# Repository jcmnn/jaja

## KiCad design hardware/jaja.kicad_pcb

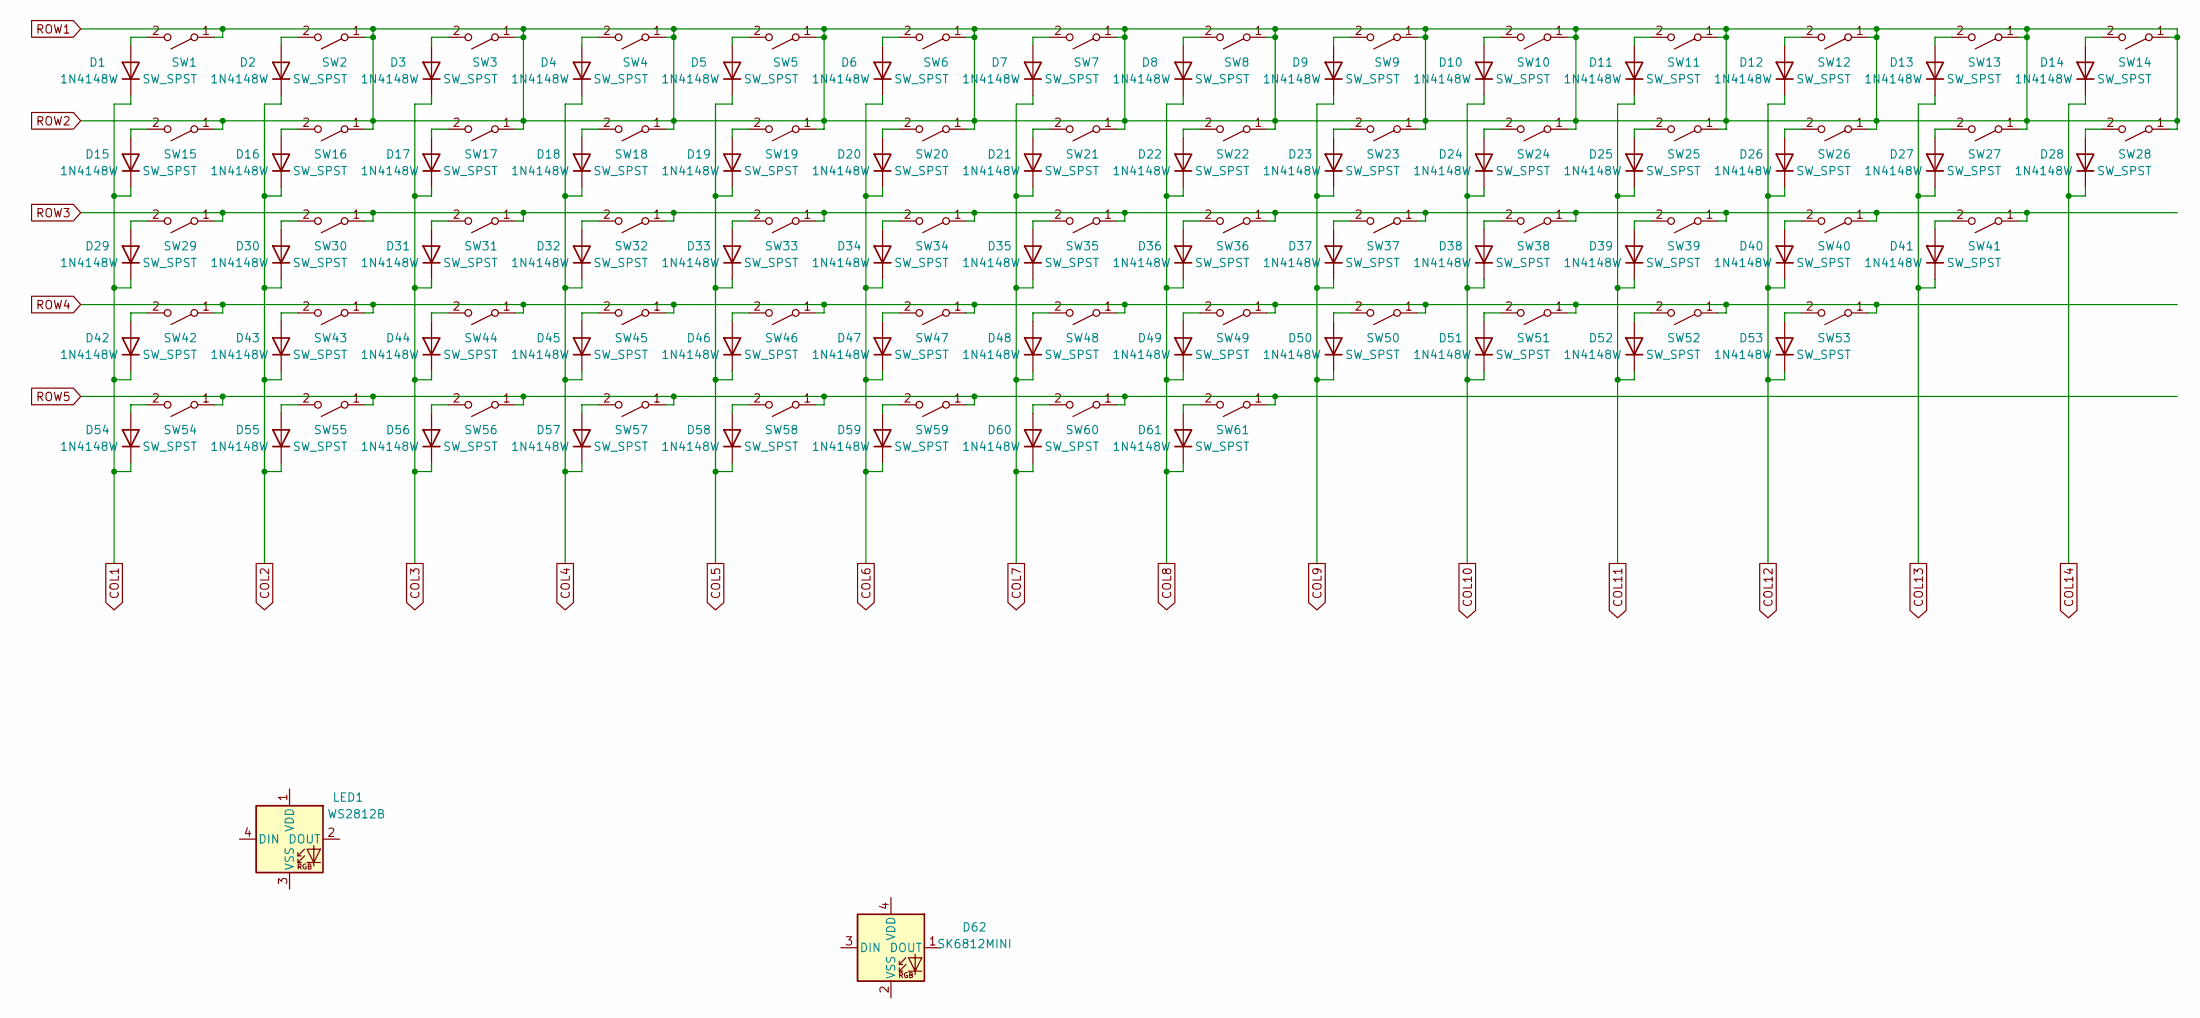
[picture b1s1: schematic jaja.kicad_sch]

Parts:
D1, D2, D3, D4, D5, D6, D7, D8, D9, D10, D11, D12, D13, D14, D15, D16, D17, D18, D19, D20, D21, D22, D23, D24, D25, D26, D27, D28, D29, D30, D31, D32, D33, D34, D35, D36, D37, D38, D39, D40, D41, D42, D43, D44, D45, D46, D47, D48, D49, D50, D51, D52, D53, D54, D55, D56, D57, D58, D59, D60, D61: 1N4148W; D_SOD-123
D62: SK6812MINI; SK6812-MINI-E
LED1: WS2812B; LED_WS2812B_PLCC4_5.0x5.0mm_P3.2mm
SW1, SW2, SW3, SW4, SW5, SW6, SW7, SW8, SW9, SW10, SW11, SW12, SW13, SW16, SW17, SW18, SW19, SW20, SW21, SW22, SW23, SW24, SW25, SW26, SW27, SW30, SW31, SW32, SW33, SW34, SW35, SW36, SW37, SW38, SW39, SW40, SW43, SW44, SW45, SW46, SW47, SW48, SW49, SW50, SW51, SW52: SW_SPST; SW_Hotswap_Kailh_MX_plated_1.00u
SW14: SW_SPST; SW_Hotswap_Kailh_MX_plated_2.00u
SW15, SW28: SW_SPST; SW_Hotswap_Kailh_MX_plated_1.50u
SW29: SW_SPST; SW_Hotswap_Kailh_MX_plated_1.75u
SW41, SW42: SW_SPST; SW_Hotswap_Kailh_MX_plated_2.25u
SW53: SW_SPST; SW_Hotswap_Kailh_MX_plated_2.75u
SW54, SW55, SW56, SW58, SW59, SW60, SW61: SW_SPST; SW_Hotswap_Kailh_MX_plated_1.25u
SW57: SW_SPST; SW_Hotswap_Kailh_MX_plated_6.25u

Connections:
COL1: D1.1 (K), D15.1 (K), D29.1 (K), D42.1 (K), D54.1 (K)
COL2: D2.1 (K), D16.1 (K), D30.1 (K), D43.1 (K), D55.1 (K)
COL3: D3.1 (K), D17.1 (K), D31.1 (K), D44.1 (K), D56.1 (K)
COL4: D4.1 (K), D18.1 (K), D32.1 (K), D45.1 (K), D57.1 (K)
COL5: D5.1 (K), D19.1 (K), D33.1 (K), D46.1 (K), D58.1 (K)
COL6: D6.1 (K), D20.1 (K), D34.1 (K), D47.1 (K), D59.1 (K)
COL7: D7.1 (K), D21.1 (K), D35.1 (K), D48.1 (K), D60.1 (K)
COL8: D8.1 (K), D22.1 (K), D36.1 (K), D49.1 (K), D61.1 (K)
COL9: D9.1 (K), D23.1 (K), D37.1 (K), D50.1 (K)
COL10: D10.1 (K), D24.1 (K), D38.1 (K), D51.1 (K)
COL11: D11.1 (K), D25.1 (K), D39.1 (K), D52.1 (K)
COL12: D12.1 (K), D26.1 (K), D40.1 (K), D53.1 (K)
COL13: D13.1 (K), D27.1 (K), D41.1 (K)
COL14: D14.1 (K), D28.1 (K)
unnamed: D1.2 (A), SW1.2 (B)
unnamed: D2.2 (A), SW2.2 (B)
unnamed: D3.2 (A), SW3.2 (B)
unnamed: D4.2 (A), SW4.2 (B)
unnamed: D5.2 (A), SW5.2 (B)
unnamed: D6.2 (A), SW6.2 (B)
unnamed: D7.2 (A), SW7.2 (B)
unnamed: D8.2 (A), SW8.2 (B)
unnamed: D9.2 (A), SW9.2 (B)
unnamed: D10.2 (A), SW10.2 (B)
unnamed: D11.2 (A), SW11.2 (B)
unnamed: D12.2 (A), SW12.2 (B)
unnamed: D13.2 (A), SW13.2 (B)
unnamed: D14.2 (A), SW14.2 (B)
unnamed: D15.2 (A), SW15.2 (B)
unnamed: D16.2 (A), SW16.2 (B)
unnamed: D17.2 (A), SW17.2 (B)
unnamed: D18.2 (A), SW18.2 (B)
unnamed: D19.2 (A), SW19.2 (B)
unnamed: D20.2 (A), SW20.2 (B)
unnamed: D21.2 (A), SW21.2 (B)
unnamed: D22.2 (A), SW22.2 (B)
unnamed: D23.2 (A), SW23.2 (B)
unnamed: D24.2 (A), SW24.2 (B)
unnamed: D25.2 (A), SW25.2 (B)
unnamed: D26.2 (A), SW26.2 (B)
unnamed: D27.2 (A), SW27.2 (B)
unnamed: D28.2 (A), SW28.2 (B)
unnamed: D29.2 (A), SW29.2 (B)
unnamed: D30.2 (A), SW30.2 (B)
unnamed: D31.2 (A), SW31.2 (B)
unnamed: D32.2 (A), SW32.2 (B)
unnamed: D33.2 (A), SW33.2 (B)
unnamed: D34.2 (A), SW34.2 (B)
unnamed: D35.2 (A), SW35.2 (B)
unnamed: D36.2 (A), SW36.2 (B)
unnamed: D37.2 (A), SW37.2 (B)
unnamed: D38.2 (A), SW38.2 (B)
unnamed: D39.2 (A), SW39.2 (B)
unnamed: D40.2 (A), SW40.2 (B)
unnamed: D41.2 (A), SW41.2 (B)
unnamed: D42.2 (A), SW42.2 (B)
unnamed: D43.2 (A), SW43.2 (B)
unnamed: D44.2 (A), SW44.2 (B)
unnamed: D45.2 (A), SW45.2 (B)
unnamed: D46.2 (A), SW46.2 (B)
unnamed: D47.2 (A), SW47.2 (B)
unnamed: D48.2 (A), SW48.2 (B)
unnamed: D49.2 (A), SW49.2 (B)
unnamed: D50.2 (A), SW50.2 (B)
unnamed: D51.2 (A), SW51.2 (B)
unnamed: D52.2 (A), SW52.2 (B)
unnamed: D53.2 (A), SW53.2 (B)
unnamed: D54.2 (A), SW54.2 (B)
unnamed: D55.2 (A), SW55.2 (B)
unnamed: D56.2 (A), SW56.2 (B)
unnamed: D57.2 (A), SW57.2 (B)
unnamed: D58.2 (A), SW58.2 (B)
unnamed: D59.2 (A), SW59.2 (B)
unnamed: D60.2 (A), SW60.2 (B)
unnamed: D61.2 (A), SW61.2 (B)
ROW1: SW1.1 (A), SW2.1 (A), SW3.1 (A), SW4.1 (A), SW5.1 (A), SW6.1 (A), SW7.1 (A), SW8.1 (A), SW9.1 (A), SW10.1 (A), SW11.1 (A), SW12.1 (A), SW13.1 (A), SW14.1 (A), SW15.1 (A), SW16.1 (A), SW17.1 (A), SW18.1 (A), SW19.1 (A), SW20.1 (A), SW21.1 (A), SW22.1 (A), SW23.1 (A), SW24.1 (A), SW25.1 (A), SW26.1 (A), SW27.1 (A), SW28.1 (A)
ROW3: SW29.1 (A), SW30.1 (A), SW31.1 (A), SW32.1 (A), SW33.1 (A), SW34.1 (A), SW35.1 (A), SW36.1 (A), SW37.1 (A), SW38.1 (A), SW39.1 (A), SW40.1 (A), SW41.1 (A)
ROW4: SW42.1 (A), SW43.1 (A), SW44.1 (A), SW45.1 (A), SW46.1 (A), SW47.1 (A), SW48.1 (A), SW49.1 (A), SW50.1 (A), SW51.1 (A), SW52.1 (A), SW53.1 (A)
ROW5: SW54.1 (A), SW55.1 (A), SW56.1 (A), SW57.1 (A), SW58.1 (A), SW59.1 (A), SW60.1 (A), SW61.1 (A)

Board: 2 copper layers, 124 parts (0 on the bottom side), 79 nets, no tracks yet.

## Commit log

2023-04-08 Add key switches
2023-04-09 Add LED library
